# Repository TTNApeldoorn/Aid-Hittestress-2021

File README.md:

# Aid-Hittestress-2021

## About this repository
This repository holds all information te build de AiD-Heatstress-sensor. 

**At this moment the repository presents work in progress. Changes may accur any time without notice!!**

# Disclaimer
The documentation of the TTN-Apeldoorn Aid-Hittestress-2021 sensor is distributed in the hope that it will be useful, but WITHOUT ANY WARRANTY; without even the 
implied warranty of MERCHANTABILITY or FITNESS FOR A PARTICULAR PURPOSE.

# License
The TTN-Apeldoorn Aid-Hittestress-2021 sensor is free soft- and hardware:
you can redistribute and/or modify it under the terms of a Creative Commons Attribution-NonCommercial 4.0 International License (http://creativecommons.org/licenses/by-nc/4.0/) by TTN-Apeldoorn (https://www.thethingsnetwork.org/community/apeldoorn/) E-mail: ttnapeldoorncoreteam@rfsee.nl

<br />This work is licensed under a <a rel="license" href="http://creativecommons.org/licenses/by-nc/4.0/">Creative Commons Attribution-NonCommercial 4.0 International License</a>.

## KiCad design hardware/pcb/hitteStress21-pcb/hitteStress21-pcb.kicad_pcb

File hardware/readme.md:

# Hardware for Hittestress 2021 node.

## Documentation

## PCB design

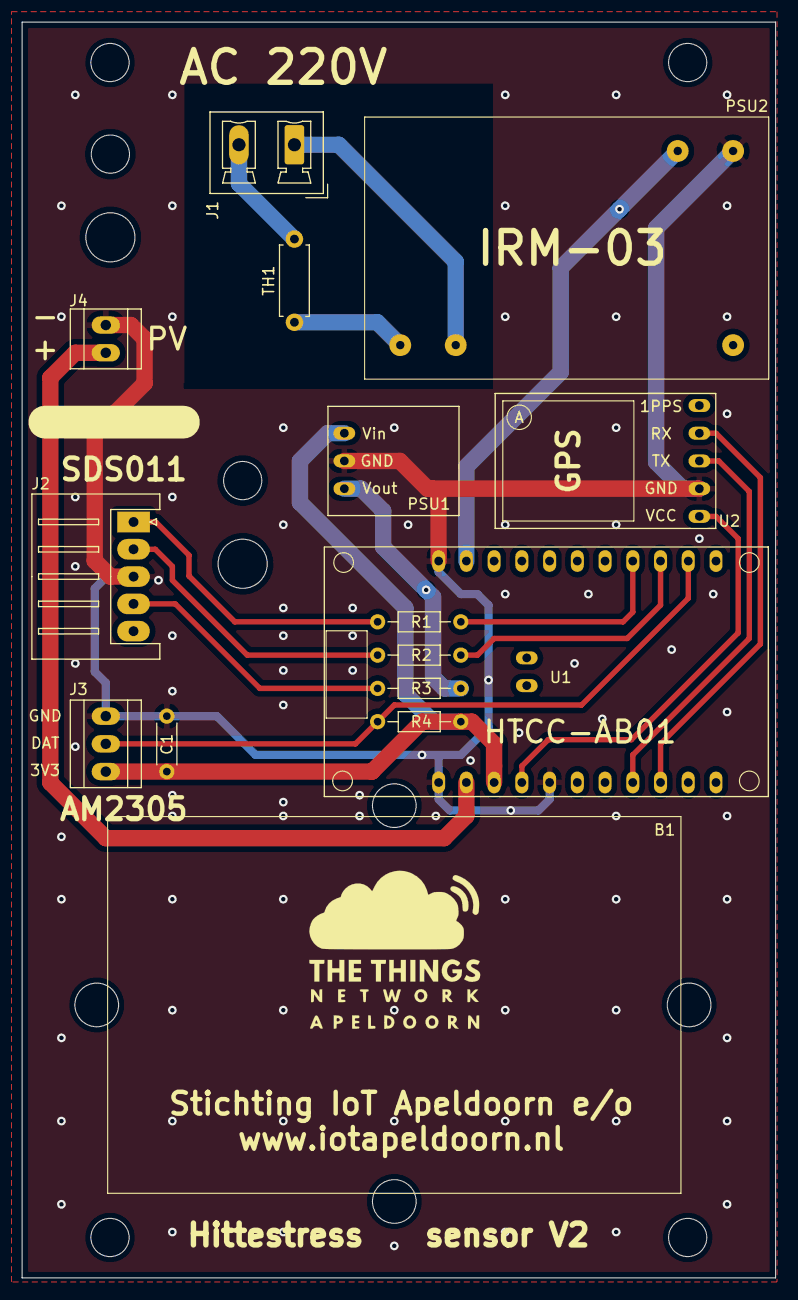
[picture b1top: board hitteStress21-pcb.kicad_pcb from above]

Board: 2 copper layers, 68.9 x 114.9 mm, 15 parts (0 on the bottom side), 17 nets.

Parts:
B1: LiPo_3V7; LiPo_3V7_2000mAh_JST-PH
C1: 10u; R_Axial_DIN0204_L3.6mm_D1.6mm_P5.08mm_Horizontal
J1: Conn_01x02_Female; PhoenixContact_MCV_1,5_2-G-5.08_1x02_P5.08mm_Vertical
J2: Conn_01x05; JST_XH_S5B-XH-A_1x05_P2.50mm_Horizontal
J3: Conn_01x03; Wurth_2109_p2.54
J4: Conn_01x02; Wurth_2109_P2.54_2x1
PSU1: MINIDCDCBOOST5V; MINIDCBOOST5V
PSU2: IRM-03
R1, R2: 1k; R_Axial_DIN0204_L3.6mm_D1.6mm_P7.62mm_Horizontal
R3: 4R7; R_Axial_DIN0204_L3.6mm_D1.6mm_P7.62mm_Horizontal
R4: 5k1; R_Axial_DIN0204_L3.6mm_D1.6mm_P7.62mm_Horizontal
TH1: Thermistor; R_Axial_DIN0207_L6.3mm_D2.5mm_P7.62mm_Horizontal
U1: HTCC-AB01
U2: GPS

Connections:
/3V3: C1.1, J3.1, PSU1.1, R4.2, U1.9
/3V3_EXT: U1.8, U2.1
/5V: PSU2.3, U1.13
/5V_EXT: PSU1.3, R3.2
/AM2305_DATA: J3.2, R4.1, U1.21
/GPS_RXD: U1.3, U2.4
/GPS_TXD: U1.4, U2.3
/PM_RX: J2.1, R1.1
/PM_TX: J2.2, R2.1
/PV: J4.1, U1.10
/SDS011_RXD: R2.2, U1.20
/SDS011_TXD: R1.2, U1.19
GND: C1.2, J2.3, J3.3, J4.2, PSU1.2, PSU2.5, U1.7, U1.11, U1.12, U2.2
unnamed: J1.1, PSU2.2
unnamed: J1.2, TH1.2
unnamed: J2.4, R3.1
unnamed: PSU2.1, TH1.1

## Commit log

2021-01-13 Update; PCB schema versie:001
2021-01-13 Added documentation
2021-01-13 Update LoraNode.ino
    Cycle time and GPS cycle updated
2021-01-13 PCB design step
2021-01-16 Updates on footprints
2021-01-17 PCB design updates
2021-02-16 Modified HTCC-AB01 footprint and updated PCB accordingly
2021-02-18 UPdate PCD, added support holes for antenna supports
2021-03-19 Added optional housing
2021-04-06 Start redesign PCB
2021-04-07 Update PCB
2021-04-08 Added frame for SDS011
2021-04-14 Added drill plan
2021-04-16 Added drill drawing
2021-04-25 Update LoraNode.ino
    measurement and status message separated
2021-04-28 Added schema
2021-04-28 Added component layout
2021-04-28 Merged branch
2021-06-18 update to V1.2
    - LiPO protection added, operation starts if Lipo is > 3.8v and goes in deepsleep if Lipo < 3.7v
    - wake-up SDS ipmproved
    - Switching between 2 soft serials ports improved
2021-10-19 Major update to V1.5
    New Heltec Framework V1.3 used
    Hang situation solved
    Battery management improved
2021-10-19 major update to V1.5
2021-10-19 HW diagram adapted
    AM2305 changed from 3.3Vtot 5V
    Elco's added, to absorb the switch-on current of the fan of the SDS011
